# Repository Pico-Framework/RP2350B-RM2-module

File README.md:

# RP2350B-RM2-Module

A compact RP2350B-based wireless module integrating:

- Raspberry Pi RP2350B
- RM2 Wi-Fi/Bluetooth module
- QSPI flash
- QSPI PSRAM
- USB-C
- Onboard voltage-regulator, capable of being disabled for production
- Single-sided design for automated production
- Castellated edges for embedded integration
- SWD debug support

The board is designed as a production-capable embedded module with integrated development convenience.

## Features

- RP2350B MCU
- RM2 wireless module
- 3.3V operation
- QSPI flash
- QSPI PSRAM
- USB device support
- Castellated module form factor
- JLCPCB assembly friendly
- Open hardware

## Status

Early prototype development.

## Repository Contents

- KiCad hardware design files
- Schematics
- PCB layout
- BOM and assembly data
- Production outputs

## Assembly Notes

Current prototype strategy:

- JLCPCB assembly for core board components
- Manual assembly of RM2 and PSRAM components

## License

MIT License

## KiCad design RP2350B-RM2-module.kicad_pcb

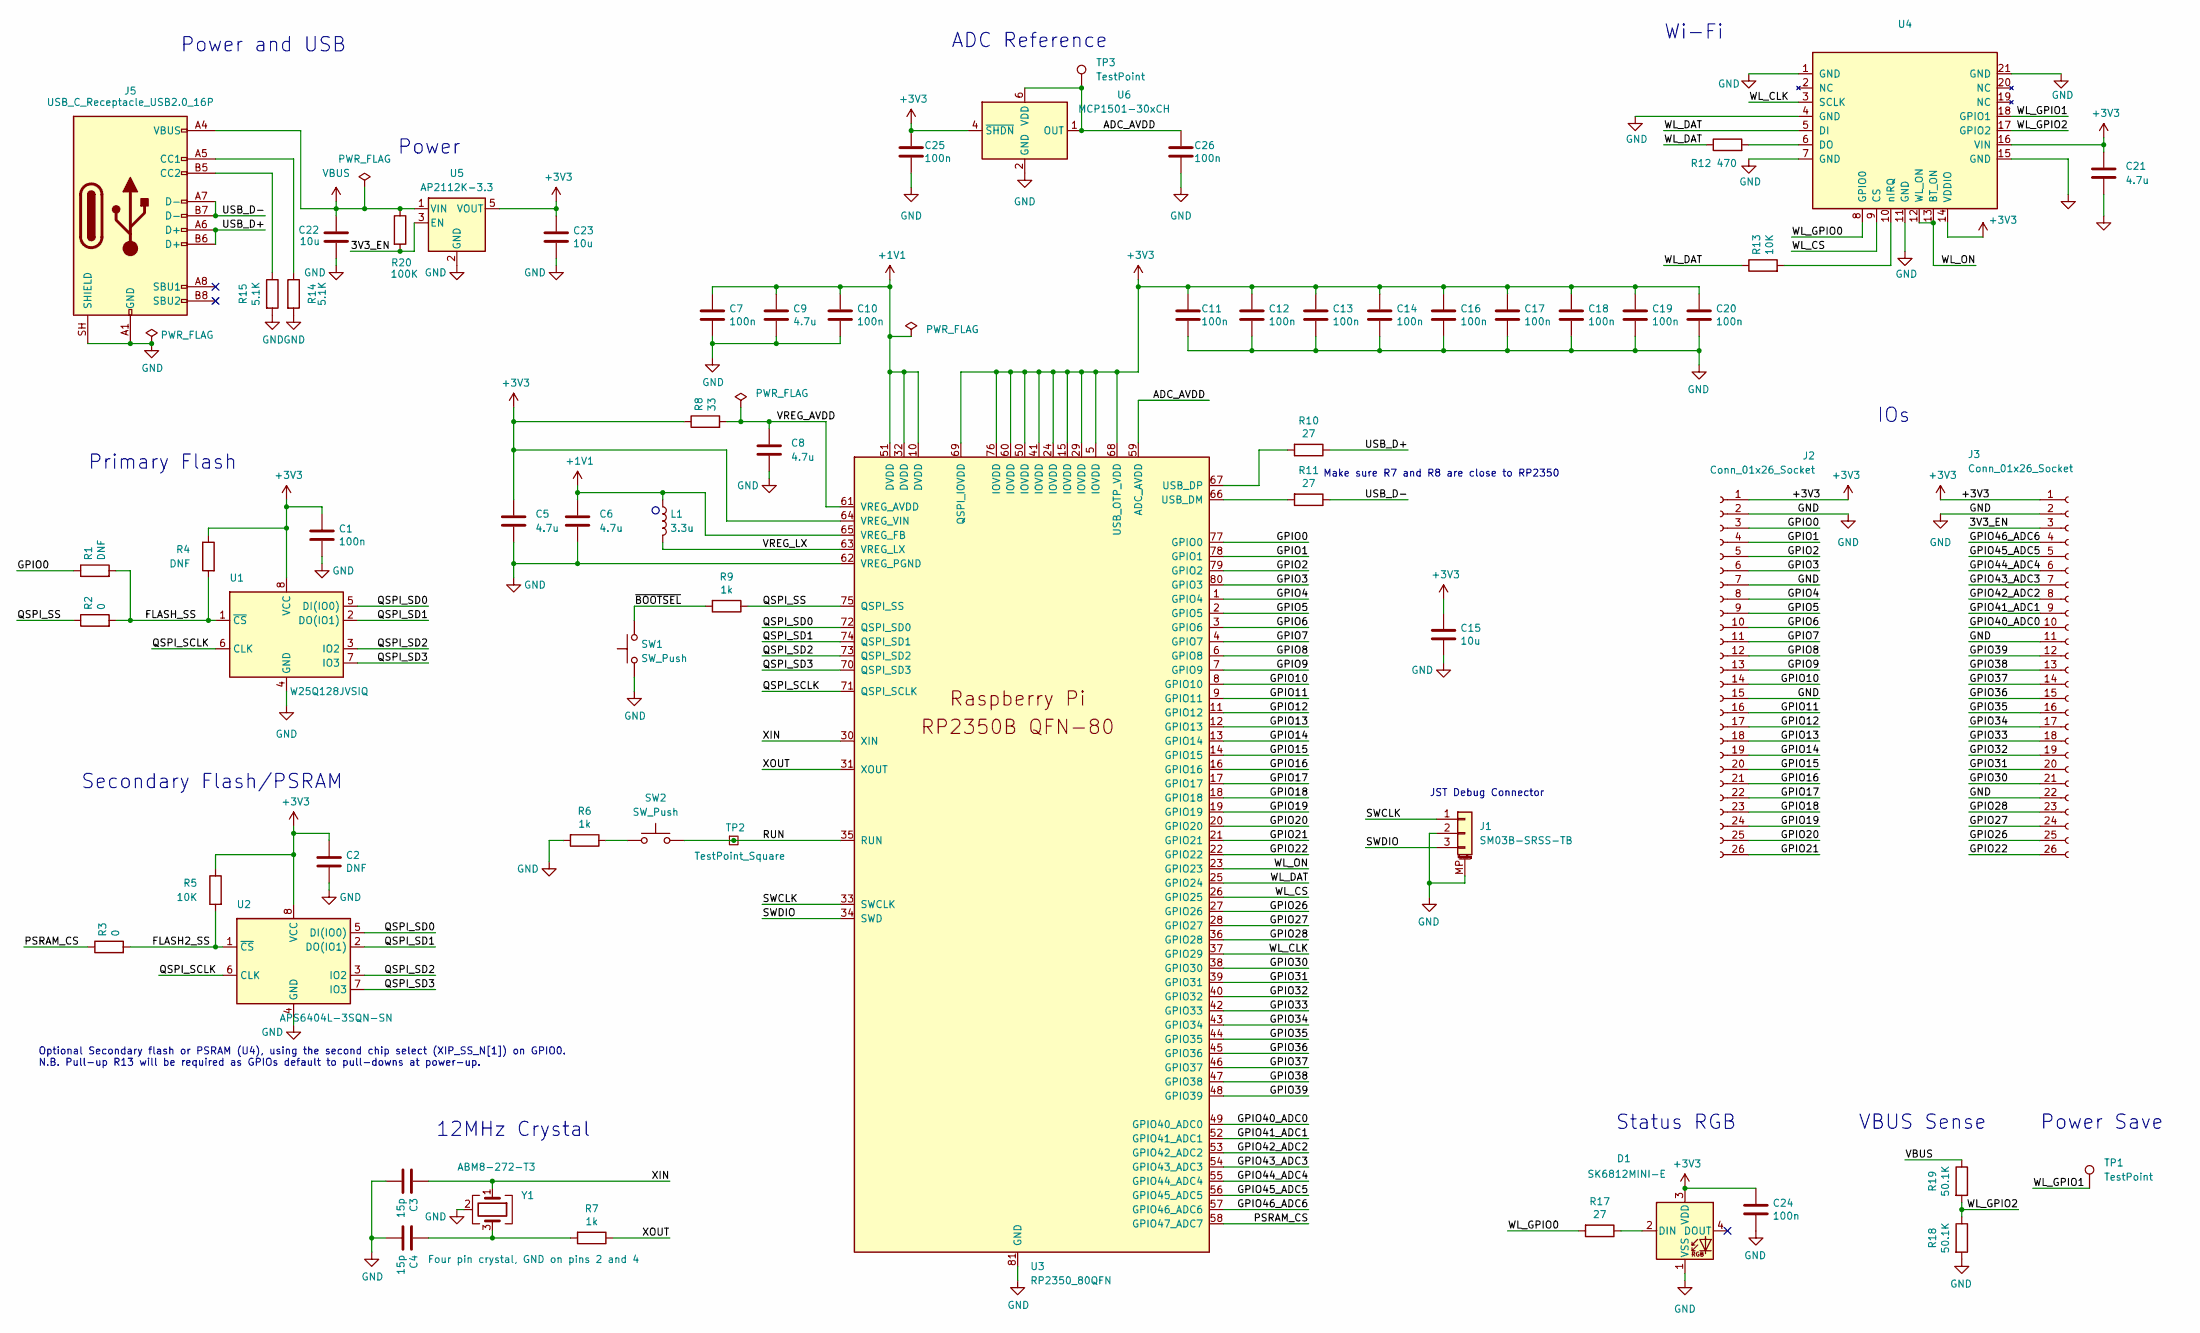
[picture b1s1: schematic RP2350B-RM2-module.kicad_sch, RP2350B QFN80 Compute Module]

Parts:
C1, C7, C10, C11, C12, C13, C14, C16, C17, C18, C19, C20, C24, C25, C26: 100n; C_0402_1005Metric
C2: DNF; C_0402_1005Metric
C3, C4: 15p; C_0402_1005Metric
C5, C6, C21: 4.7u; C_0402_1005Metric_small_pads
C8, C9: 4.7u; C_0402_1005Metric
C15, C22, C23: 10u; C_0805_2012Metric
D1: SK6812MINI-E; LED_SK6812MINI-E_3.2x2.8mm_P1.5mm_ReverseMount
J1: SM03B-SRSS-TB; JST_SH_BM03B-SRSS-TB_1x03-1MP_P1.00mm_Vertical
J2: Conn_01x26_Socket; Castellated_26_pins_left_side
J3: Conn_01x26_Socket; Castellated_26_pins
J5: USB_C_Receptacle_USB2.0_16P; USB_C_Receptacle_XKB_U262-16XN-4BVC11; Part Number U262-161N-4BVC11; JLCPCB C319148
L1: 3.3u; L_pol_2016
R1, R4: DNF; R_0402_1005Metric
R2, R3: 0; R_0402_1005Metric
R5, R13: 10K; R_0402_1005Metric
R6, R7, R9: 1k; R_0402_1005Metric
R8: 33; R_0402_1005Metric
R10, R11, R17: 27; R_0402_1005Metric
R12: 470; R_0402_1005Metric
R14, R15: 5.1K; R_0402_1005Metric
R18, R19: 50.1K; R_0402_1005Metric
R20: 100K; R_0402_1005Metric
SW1, SW2: SW_Push; SW_Push_1P1T_NO_Vertical_Wuerth_434133025816
TP1: TestPoint; TestPoint_THTPad_D1.0mm_Drill0.5mm
TP2: TestPoint_Square; TestPoint_Pad_1.5x1.5mm
TP3: TestPoint; TestPoint_Pad_D1.5mm
U1: W25Q128JVSIQ; SOIC-8_5.3x5.3mm_P1.27mm; Part Number W25Q128JVSIQ; JLCPCB C113767
U2: APS6404L-3SQN-SN; SOP-8_3.76x4.96mm_P1.27mm; Part Number W25Q128JVSIQ; JLCPCB C113767
U3: RP2350_80QFN; RP2350-QFN-80-1EP_10x10_P0.4mm_EP3.4x3.4mm_ThermalVias; JLCPCB C42415655
U4: <value>; rpi_rmc20452t
U5: AP2112K-3.3; SOT-23-5; Part Number TPAP2112K-3.3TRG1; JLCPCB C3021085
U6: MCP1501-30xCH; SOT-23-6
Y1: ABM8-272-T3; Crystal_SMD_3225-4Pin_3.2x2.5mm

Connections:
+1V1: C6.1, C7.1, C9.1, C10.1, L1.1, U3.10 (DVDD), U3.32 (DVDD), U3.51 (DVDD), U3.65 (VREG_FB)
+3V3: C1.1, C2.1, C5.1, C11.1, C12.1, C13.1, C14.1, C15.1, C16.1, C17.1, C18.1, C19.1, C20.1, C21.1, C23.1, C24.1, C25.1, D1.3 (VDD), J2.1, J3.1, R4.1, R5.1, R8.1, U1.8 (VCC), U2.8 (VCC), U3.5 (IOVDD), U3.15 (IOVDD), U3.24 (IOVDD), U3.29 (IOVDD), U3.41 (IOVDD), U3.50 (IOVDD), U3.60 (IOVDD), U3.64 (VREG_VIN), U3.68 (USB_OTP_VDD), U3.69 (QSPI_IOVDD), U3.76 (IOVDD), U4.14 (VDDIO), U4.16 (VIN), U5.5 (VOUT), U6.4 (~SHDN)
/3V3_EN: J3.3, R20.2, U5.3 (EN)
/ADC_AVDD: C26.1, TP3.1 (1_1), U3.59 (ADC_AVDD), U6.1 (OUT), U6.6 (VDD)
/FLASH2_SS: R3.2, R5.2, U2.1 (~CS)
/FLASH_SS: R1.2, R2.2, R4.2, U1.1 (~CS)
/GPIO0: J2.3, R1.1, U3.77 (GPIO0)
/GPIO1: J2.4, U3.78 (GPIO1)
/GPIO2: J2.5, U3.79 (GPIO2)
/GPIO3: J2.6, U3.80 (GPIO3)
/GPIO4: J2.8, U3.1 (GPIO4)
/GPIO5: J2.9, U3.2 (GPIO5)
/GPIO6: J2.10, U3.3 (GPIO6)
/GPIO7: J2.11, U3.4 (GPIO7)
/GPIO8: J2.12, U3.6 (GPIO8)
/GPIO9: J2.13, U3.7 (GPIO9)
/GPIO10: J2.14, U3.8 (GPIO10)
/GPIO11: J2.16, U3.9 (GPIO11)
/GPIO12: J2.17, U3.11 (GPIO12)
/GPIO13: J2.18, U3.12 (GPIO13)
/GPIO14: J2.19, U3.13 (GPIO14)
/GPIO15: J2.20, U3.14 (GPIO15)
/GPIO16: J2.21, U3.16 (GPIO16)
/GPIO17: J2.22, U3.17 (GPIO17)
/GPIO18: J2.23, U3.18 (GPIO18)
/GPIO19: J2.24, U3.19 (GPIO19)
/GPIO20: J2.25, U3.20 (GPIO20)
/GPIO21: J2.26, U3.21 (GPIO21)
/GPIO22: J3.26, U3.22 (GPIO22)
/GPIO26: J3.25, U3.27 (GPIO26)
/GPIO27: J3.24, U3.28 (GPIO27)
/GPIO28: J3.23, U3.36 (GPIO28)
/GPIO30: J3.21, U3.38 (GPIO30)
/GPIO31: J3.20, U3.39 (GPIO31)
/GPIO32: J3.19, U3.40 (GPIO32)
/GPIO33: J3.18, U3.42 (GPIO33)
/GPIO34: J3.17, U3.43 (GPIO34)
/GPIO35: J3.16, U3.44 (GPIO35)
/GPIO36: J3.15, U3.45 (GPIO36)
/GPIO37: J3.14, U3.46 (GPIO37)
/GPIO38: J3.13, U3.47 (GPIO38)
/GPIO39: J3.12, U3.48 (GPIO39)
/GPIO40_ADC0: J3.10, U3.49 (GPIO40_ADC0)
/GPIO41_ADC1: J3.9, U3.52 (GPIO41_ADC1)
/GPIO42_ADC2: J3.8, U3.53 (GPIO42_ADC2)
/GPIO43_ADC3: J3.7, U3.54 (GPIO43_ADC3)
/GPIO44_ADC4: J3.6, U3.55 (GPIO44_ADC4)
/GPIO45_ADC5: J3.5, U3.56 (GPIO45_ADC5)
/GPIO46_ADC6: J3.4, U3.57 (GPIO46_ADC6)
/PSRAM_CS: R3.1, U3.58 (GPIO47_ADC7)
/QSPI_SCLK: U1.6 (CLK), U2.6 (CLK), U3.71 (QSPI_SCLK)
/QSPI_SD0: U1.5 (DI(IO0)), U2.5 (DI(IO0)), U3.72 (QSPI_SD0)
/QSPI_SD1: U1.2 (DO(IO1)), U2.2 (DO(IO1)), U3.74 (QSPI_SD1)
/QSPI_SD2: U1.3 (IO2), U2.3 (IO2), U3.73 (QSPI_SD2)
/QSPI_SD3: U1.7 (IO3), U2.7 (IO3), U3.70 (QSPI_SD3)
/QSPI_SS: R2.1, R9.1, U3.75 (QSPI_SS)
/RUN: SW2.2, TP2.1 (1_1), U3.35 (RUN)
/SWCLK: J1.1, U3.33 (SWCLK)
/SWDIO: J1.3, U3.34 (SWD)
/USB_D+: J5.A6 (D+), J5.B6 (D+), R10.1
/USB_D-: J5.A7 (D-), J5.B7 (D-), R11.1
/VREG_AVDD: C8.1, R8.2, U3.61 (VREG_AVDD)
/VREG_LX: L1.2, U3.63 (VREG_LX)
/WL_CLK: U3.37 (GPIO29), U4.3 (SCLK)
/WL_CS: U3.26 (GPIO25), U4.9 (CS)
/WL_DAT: R12.1, R13.1, U3.25 (GPIO24), U4.5 (DI)
/WL_GPIO0: R17.2, U4.8 (GPIO0)
/WL_GPIO1: TP1.1 (1_1), U4.18 (GPIO1)
/WL_GPIO2: R18.1, R19.2, U4.17 (GPIO2)
/WL_ON: U3.23 (GPIO23), U4.12 (WL_ON), U4.13 (BT_ON)
/XIN: C3.1, U3.30 (XIN), Y1.1
/XOUT: R7.1, U3.31 (XOUT)
/~BOOTSEL: R9.2, SW1.2
GND: C1.2, C2.2, C3.2, C4.2, C5.2, C6.2, C7.2, C8.2, C9.2, C10.2, C11.2, C12.2, C13.2, C14.2, C15.2, C16.2, C17.2, C18.2, C19.2, C20.2, C21.2, C22.2, C23.2, C24.2, C25.2, C26.2, D1.1 (VSS), J1.2, J1.MP (MountPin), J2.2, J2.7, J2.15, J3.2, J3.11, J3.22, J5.A1 (GND), J5.A12 (GND), J5.B1 (GND), J5.B12 (GND), J5.SH (SHIELD), R6.2, R14.2, R15.2, R18.2, SW1.1, U1.4 (GND), U2.4 (GND), U3.62 (VREG_PGND), U3.81 (GND), U4.1 (GND), U4.4 (GND), U4.7 (GND), U4.11 (GND), U4.15 (GND), U4.21 (GND), U5.2 (GND), U6.2 (GND), U6.3 (GND), U6.5 (GND), Y1.2 (G), Y1.4 (G)
unnamed: C4.1, R7.2, Y1.3
unnamed: D1.2 (DIN), R17.1
unnamed: J5.A5 (CC1), R14.1
unnamed: J5.B5 (CC2), R15.1
unnamed: R6.1, SW2.1
unnamed: R11.2, U3.66 (USB_DM)
unnamed: R10.2, U3.67 (USB_DP)
unnamed: R12.2, U4.6 (DO)
unnamed: R13.2, U4.10 (nIRQ)
VBUS: C22.1, J5.A4 (VBUS), J5.A9 (VBUS), J5.B4 (VBUS), J5.B9 (VBUS), R19.1, R20.1, U5.1 (VIN)

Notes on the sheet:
Optional Secondary flash or PSRAM (U4), using the second chip select (XIP_SS_N[1]) on GPIO0. N.B. Pull-up R13 will be required as GPIOs default to pull-downs at power-up.
Power
IOs
12MHz Crystal
Status RGB
Power and USB
Primary Flash
Power Save
JST Debug Connector
ADC Reference
Make sure R7 and R8 are close to RP2350
Secondary Flash/PSRAM
Wi-Fi
VBUS Sense

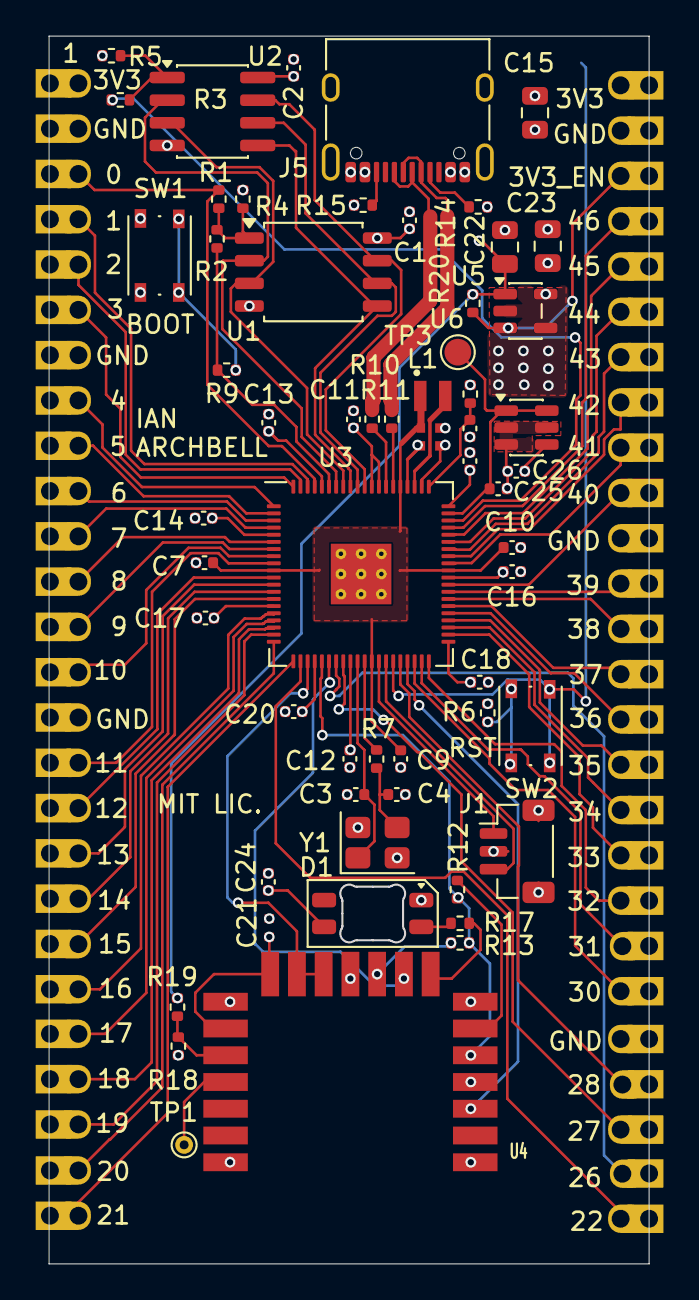
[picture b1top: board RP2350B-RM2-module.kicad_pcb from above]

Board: 4 copper layers, 33.6 x 68.8 mm, 63 parts (1 on the bottom side), 84 nets.

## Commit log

2026-05-09 Initial RP2350B RM2 module design
2026-05-09 added license and basic readme
2026-05-12 clean ERC and DRC
2026-05-12 Changed PSRAM
2026-05-12 Added ADC vref
2026-05-13 Added pin numbering
